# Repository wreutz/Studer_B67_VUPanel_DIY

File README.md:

# Studer B67 VUPanel DIY

Studer B67 VU Panel do-it-yourself clone: as i couldn't find a VU Panel for my Studer B67 MK I i had to build it based on the Studer Service Manual myself.

Parts so far:

* Overload detector card
* Attentuator board
* Headphone board
* Switch board
* Service extension card (to calibrate cards in the machine)

For all these parts there are ready made files to send your PCB manufacturer (i used JLCPCB) in the [CAM](CAM) folder.

[KiCad](KiCad) folder contains the KiCad V5 source projects for the PCBs. BOM files as interactive HTML files to ease populating of the boards and BOM files in Excel format with links to distributors are included.

The [frontpanel](Frontpanel) folder contains the DXF file i used to laser a prototype frontpanel in 4 mm acrylic and the distance rings for the sleepy eyes switches as .stl files and .gcode for my Velleman K8400 3D printer.

As a goodie there are the 3D Printer files for a tape cutting block in the [misc](misc) folder.

## Schematics and PCBs

If you don't have KiCad installed you can get the schematic files and PCBs as PDFs here:

 [Attentuator_Board_V2_PCB.pdf](./schematics_pcbs_PDF/Attentuator_Board_V2_PCB.pdf) 

 [Attentuator_Board_V2_Schematic.pdf](./schematics_pcbs_PDF/Attentuator_Board_V2_Schematic.pdf) 

 [Headphone_Board_PCB.pdf](./schematics_pcbs_PDF/Headphone_Board_PCB.pdf) 

 [Headphone_Board_Schematic.pdf](schematics_pcbs_PDF/Headphone_Board_Schematic.pdf) 

 [Overload_Detector_Card_PCB.pdf](schematics_pcbs_PDF/Overload_Detector_Card_PCB.pdf) 

 [Overload_Detector_Card_Schematic.pdf](schematics_pcbs_PDF/Overload_Detector_Card_Schematic.pdf) 

 [Switch_Board_PCB.pdf](schematics_pcbs_PDF/Switch_Board_PCB.pdf) 

 [Switch_Board_Schematic.pdf](schematics_pcbs_PDF/Switch_Board_Schematic.pdf) 

## PCBs

Overload detector card:

Attentuator board:

Headphone board:

Switch board:

## Support

If you're having any problem or question, please [create an issue](https://github.com/wreutz/Studer_B67_VUPanel_DIY/issues/new) on GitHub and I'm happy to help.

## License

This repository is freeware and may be redistributed under the terms specified in the [license](LICENSE).

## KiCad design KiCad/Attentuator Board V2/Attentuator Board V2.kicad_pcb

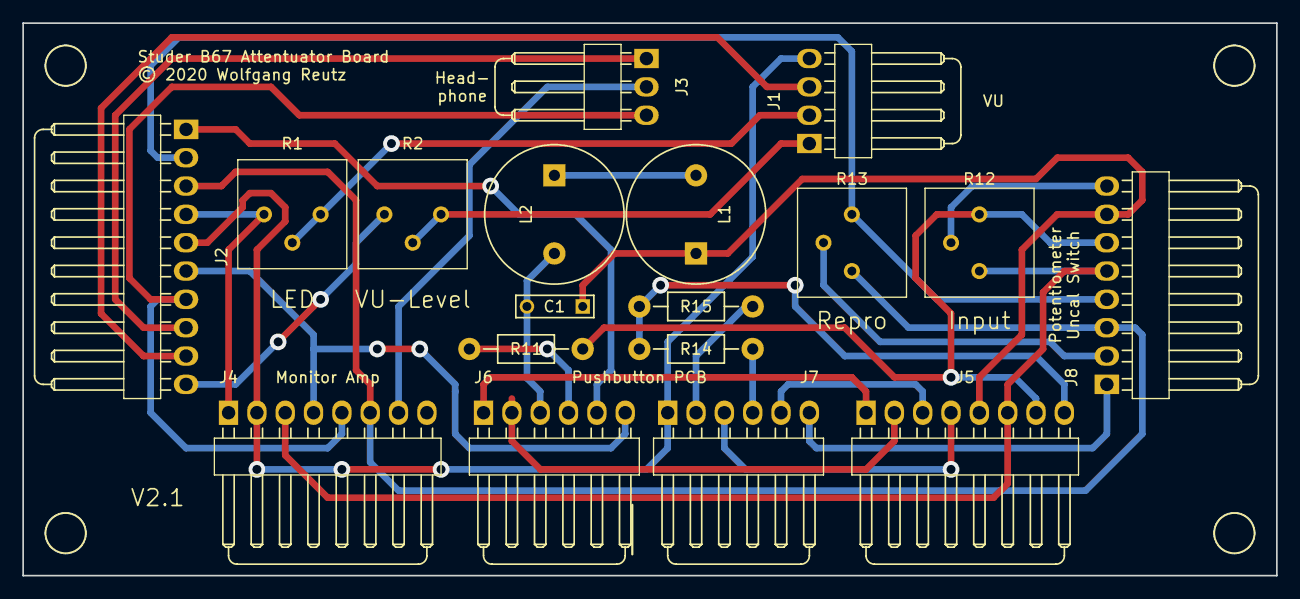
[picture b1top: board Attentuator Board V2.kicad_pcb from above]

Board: 2 copper layers, 112.4 x 49.5 mm, 18 parts (0 on the bottom side), 29 nets.

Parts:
C1: 560p; C_Rect_L7_W2_P5
J1: Conn_01x04; Molex_KK-254_1x04_P2.54mm_Horizontal
J2: Conn_01x10; Molex_KK-254_1x10_P2.54mm_Horizontal
J3: Conn_01x03; Molex_KK-254_1x03_P2.54mm_Horizontal
J4, J5, J8: Conn_01x08; Molex_KK-254_1x08_P2.54mm_Horizontal
J6, J7: Conn_01x06; Molex_KK-254_1x06_P2.54mm_Horizontal
L1, L2: 1 mH; INDUCTOR_09HCP
R1, R2, R12, R13: 10k; Potentiometer_Bourns_3386P_Vertical
R11: 10k; Resistor_Horizontal_RM10mm
R14, R15: 100; Resistor_Horizontal_RM10mm

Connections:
unnamed: C1.1, J5.5, J8.7, L1.1
unnamed: C1.2, J6.3, L2.2
unnamed: J1.1, R2.2, R2.3
unnamed: J1.2, R1.2, R1.3
unnamed: J1.3, J2.9
unnamed: J1.4, J2.5, J4.2, J7.1
unnamed: J2.1, J6.5
unnamed: J2.2, J8.4, R13.1
unnamed: J2.3, J4.6, J8.3, R13.3
unnamed: J2.4, J4.1, R1.1
unnamed: J2.6, J4.4, J6.6
unnamed: J2.7, J3.3, J4.5
unnamed: J2.8, J3.1
unnamed: J2.10, R2.1
unnamed: J3.2, J4.7
unnamed: J4.3, J5.6, J8.5, R12.3
unnamed: J5.1, J6.1
unnamed: J5.2, J6.2
unnamed: J5.3, J7.5
unnamed: J5.4, J7.3
unnamed: J5.7, J8.6, R11.1, R12.1
unnamed: J5.8, R14.1, R15.1
unnamed: J6.4, R11.2
unnamed: J7.2, R15.2
unnamed: J7.4, R14.2
unnamed: J7.6, J8.1
unnamed: J8.2, R13.2
unnamed: J8.8, R12.2
unnamed: L1.2, L2.1

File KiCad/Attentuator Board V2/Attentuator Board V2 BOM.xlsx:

Designator | Package | Quantity | Designation | Supplier 1 | Reference 1 | Price 1 | Price I | Link 1
C1 | Capacitor MKS | 1 | 560p | Reichelt | KERKO 560P | 0.05 | 0.05 | https://www.reichelt.de/keramik-kondensator-560p-kerko-560p-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
J1 | Connector | 1 | Conn_01x04 | Reichelt | MOLEX 22272041 | 0.28000000000000003 | 0.28000000000000003 | https://www.reichelt.de/at/de/molex-stiftleiste-kk-1x4-polig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
J2 | Connector | 1 | Conn_01x10 | Reichelt | MOLEX 22272101 | 0.45 | 0.45 | https://www.reichelt.de/at/de/molex-stiftleiste-kk-1x10-poli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
J3 | Connector | 1 | Conn_01x03 | Reichelt | MOLEX 22272031 | 0.2 | 0.2 | https://www.reichelt.de/at/de/molex-stiftleiste-kk-1x3-polig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
J4,J5,J8 | Connector | 3 | Conn_01x08 | Reichelt | MOLEX 22272081 | 0.34 | 1.02 | https://www.reichelt.de/at/de/molex-stiftleiste-kk-1x8-polig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
J6,J7 | Connector | 2 | Conn_01x06 | Reichelt | MOLEX 22272061 | 0.28000000000000003 | 0.56000000000000005 | https://www.reichelt.de/at/de/molex-stiftleiste-kk-1x6-polig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
L1,L2 | Inductor | 2 | 1 mH | Reichelt | L-09HCP 1,0M | 0.55000000000000004 | 1.1000000000000001 | https://www.reichelt.de/stehende-induktivitaet-09hcp-ferrit-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
R1,R2,R12,R13 | Potentiometer Trim | 4 | 10k | Reichelt | 76-10 10K | 0.27 | 1.08 | https://www.reichelt.de/praezisionspotentiometer-trimmer-lie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
R11 | Resistor | 1 | 10k | Reichelt | METALL 10K | 8.3000000000000004E-2 | 8.3000000000000004E-2 | https://secure.reichelt.at/widerstand-metallschicht-10-0-koh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
R14,R15 | Resistor | 2 | 100 | Reichelt | METALL 100 | 8.3000000000000004E-2 | 0.16600000000000001 | https://secure.reichelt.at/widerstand-metallschicht-100-ohm-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
Total |  |  |  |  |  |  | 4.9890000000000008
Board Quantity 2! -> Total Price = |  | 9.9780000000000015

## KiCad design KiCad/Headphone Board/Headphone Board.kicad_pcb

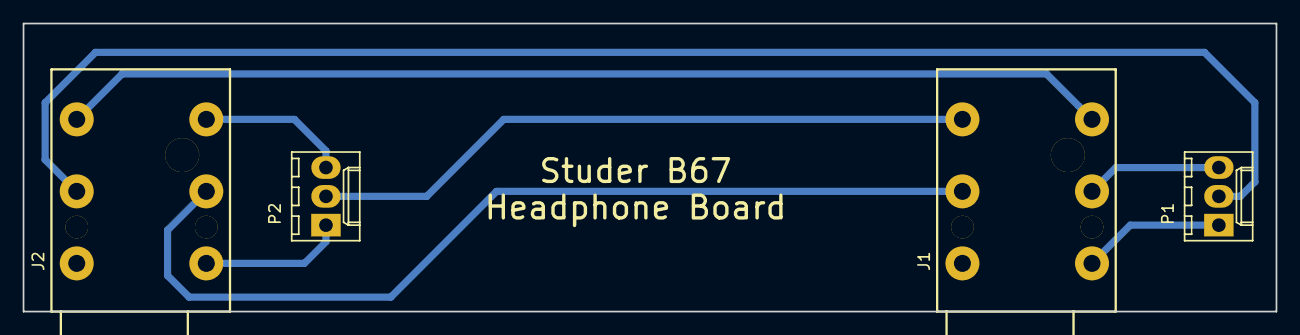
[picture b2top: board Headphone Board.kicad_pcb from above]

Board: 2 copper layers, 110.5 x 25.4 mm, 4 parts (0 on the bottom side), 8 nets.

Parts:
J1, J2: JACK_TRS_6PINS; NEUTRIK-NRJ6HF
P1, P2: CONN_01X03; Molex_KK-6410-03_03x2.54mm_Straight

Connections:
unnamed: J1.1, P1.1
unnamed: J1.2, J2.5
unnamed: J1.3, P1.3
unnamed: J1.5, P2.2
unnamed: J1.6, J2.3
unnamed: J2.1, P2.1
unnamed: J2.2, P2.3
unnamed: J2.6, P1.2

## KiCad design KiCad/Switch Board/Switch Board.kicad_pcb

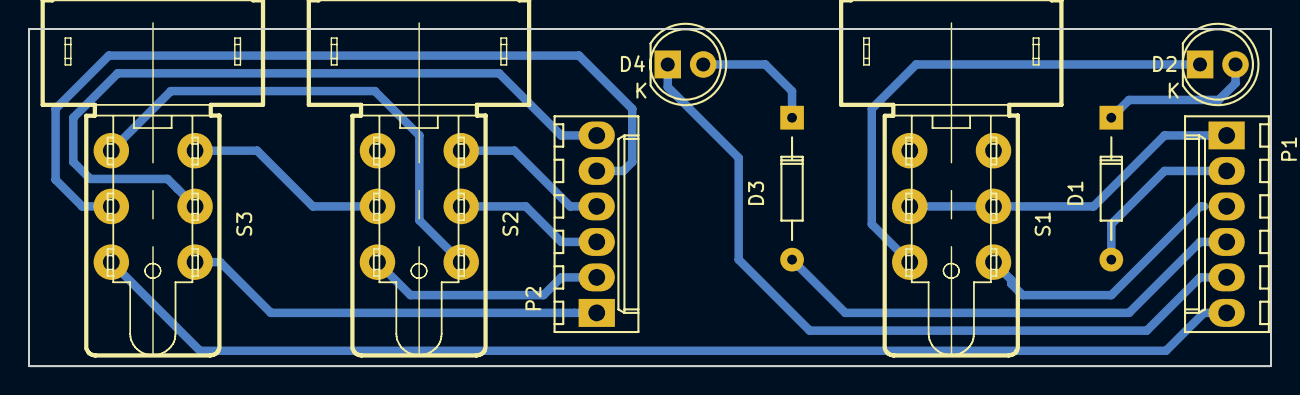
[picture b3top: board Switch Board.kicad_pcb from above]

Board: 2 copper layers, 88.9 x 24.1 mm, 9 parts (0 on the bottom side), 17 nets.

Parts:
D1, D3: 1N4448; Diode_DO-35_SOD27_Horizontal_RM10
D2, D4: LED; LED-5MM
P1, P2: CONN_01X06; Molex_KK-6410-06_06x2.54mm_Straight
S1, S2, S3: SA-200; ZFSA200

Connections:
unnamed: D1.1, D2.2
unnamed: D1.2, P1.2
unnamed: D2.1, S1.22
unnamed: D3.1, D4.2
unnamed: D3.2, P1.4
unnamed: D4.1, P1.5
unnamed: P1.1, S1.10, S1.20
unnamed: P1.3, S1.12
unnamed: P1.6, S3.22
unnamed: P2.1, S3.12
unnamed: P2.2, S2.22
unnamed: P2.3, S2.10
unnamed: P2.4, S2.11
unnamed: P2.5, S3.20
unnamed: P2.6, S3.10
unnamed: S2.12, S3.21
unnamed: S2.20, S3.11

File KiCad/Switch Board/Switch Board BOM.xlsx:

Designator | Package | Quantity | Designation | Supplier 1 | Reference 1 | Price 1 | Price I | Link 1
P1,P2 | Connector | 2 | CONN_01X06 | Reichelt | MOLEX 22272061 | 0.26 | 0.52 | https://secure.reichelt.at/molex-stiftleiste-kk-1x6-polig-st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
D2 | LED | 1 | 5 mm Green | Reichelt | LED 5MM ST GN | 0.12 | 0.12 | https://secure.reichelt.at/led-5-mm-bedrahtet-gruen-20-mcd-6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
D4 | LED | 1 | 5 mm Red | Reichelt | LED 5MM ST RT | 0.121 | 0.121 | https://secure.reichelt.at/led-5-mm-bedrahtet-rot-5-mcd-60-l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
D1,D3 | Diode | 2 | 1N4448 | Reichelt | 1N 4448 | 0.02 | 0.04 | https://secure.reichelt.at/gleichrichterdiode-100-v-0-15-a-d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
S1 | Schlafaugentaster | 1 | SA-200 Green | Reichelt | SA 200 GN | 6.35 | 6.35 | https://secure.reichelt.at/tastenschalter-2x-um-gruen-sa-200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
S2,S3 | Schlafaugentaster | 2 | SA-200 White | Reichelt | SA 200 WS | 6.35 | 12.7 | https://secure.reichelt.at/tastenschalter-2x-um-weiss-sa-200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
Total |  |  |  |  |  |  | 19.850999999999999
Board Quantity 2! -> Total Price = |  | 39.701999999999998

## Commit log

2021-02-11 added PCBs (KiCad files) added CAM files for manufacturing added frontpanel prototype lasercut file added documentation
2021-04-01 added PDFs of schematics and PCBs for people without KiCad
2021-04-01 minor fix

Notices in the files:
KiCad/Attentuator Board V2/Attentuator Board V2.kicad_pcb:
© 2020 Wolfgang Reutz
